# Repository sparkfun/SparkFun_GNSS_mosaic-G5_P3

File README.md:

SparkFun Allband GNSS RTK Breakout - mosaic-G5 P3
========================================

[*SparkFun Allband GNSS RTK Breakout - mosaic-G5 P3 (GPS-29208)*](https://www.sparkfun.com/sparkfun-allband-gnss-rtk-breakout-mosaic-g5-p3.html)

This SparkFun Allband GNSS RTK Breakout features the Septentrio mosaic-G5 P3 GNSS module, a 60% smaller and 40% lower power consumption variant of the mosaic-X5 GNSS module, making it ideal for drone and IoT applications. The receiver supports the GPS (USA), GLONASS (Russia), Beidou (China), Galileo (Europe), and QZSS (Japan) GNSS constellations, including regional systems *(i.e. SBAS)*. With its Real-Time Kinematics (RTK) capabilities, the module can achieve a horizontal accuracy of 6mm (~0.25in), vertical accuracy of 1cm (~0.4in), PPS timing resolution of 1.4ns (1.4 billionths of a second), and event trigger accuracy below 3ns. It also features Septentrio's unique [AIM+ technology](https://www.septentrio.com/en/learn-more/advanced-positioning-technology/aim-jamming-protection) for interference mitigation and anti-spoofing, ensuring best-in-class reliability and scalable position accuracy.

The mosaic-G5 P3 GNSS module supports USB 2.0 communication and two UART interfaces; along with two GPIO, two configurable PPS outputs, and two event trigger input pins. Users can control and configure the GNSS module through a command-line interface (CLI) using the Septentrio Binary Format (SBF), NMEA, and RTCM v3.x protocols. Otherwise, users can also configure the GNSS module with Septentrio's [RxTools software application](https://www.septentrio.com/en/products/gps-gnss-receiver-software/rxtools). On the board, the `UART2` interface is also broken out to a locking JST connector and BlueSMiRF PTH header pins to attach an RF transceiver for RTK corrections.

Documentation
-------------

- **[Hookup Guide (mkdocs)](http://docs.sparkfun.com/SparkFun_GNSS_mosaic-G5_P3/)** - A hookup guide for the SparkFun mosaic-G5 P3 GNSS breakout board hosted by GitHub pages.<br>

Repository Contents
-------------------

- **[/docs](/docs/)** - Online documentation files
  - [/assets](/docs/assets/) - Assets files
    - [/3d_model](/docs/assets/3d_model/) - 3D models for the board
    - [/board_files](/docs/assets/board_files/) - Design files for the board
      - [KiCad Design Files](/docs/assets/board_files/kicad_files.zip) (.zip)
      - [Schematic](/docs/assets/board_files/schematic.pdf) (.pdf)
      - [Dimensions](/docs/assets/board_files/dimensions.pdf) (.pdf)
    - [/component_documentation](/docs/assets/component_documentation/) - Datasheets for hardware components
    - [/img/hookup_guide](/docs/assets/img/hookup_guide/) - Images for hookup guide documentation - Hookup guide images for the board
    - /Hardware - Hardware design files (.brd, .sch)
      - /Production - Production files

Product Variants
----------------

- mosaic-G5 P3:
  - [GPS-29208](https://www.sparkfun.com/sparkfun-allband-gnss-rtk-breakout-mosaic-g5-p3.html) - Allband GNSS RTK Breakout - mosaic-G5 P3
  - Flex Modules:
    - [GPS-29209](https://www.sparkfun.com/sparkpnt-gnss-flex-module-mosaic-g5-p3.html) - GNSS Flex module - mosaic-G5 P3
    - [GPS-29363](https://www.sparkfun.com/sparkpnt-gnss-flex-module-mosaic-g5-p3-im19-imu.html) - GNSS Flex module - mosaic-G5 P3 & IM19
    - [GPS-](https://www.sparkfun.com/sparkfun-gnss-flex-phat-mosaic-g5-p3.html) - GNSS Flex pHAT w/ the mosaic-G5 P3 GNSS Flex module
    - [GPS-](https://www.sparkfun.com/sparkfun-gnss-flex-phat-mosaic-g5-p3-im19-imu.html) - GNSS Flex pHAT w/ the mosaic-G5 P3 & IM19 GNSS Flex module
- mosaic-X5:
  - [GPS-23088](https://www.sparkfun.com/sparkfun-triband-gnss-rtk-breakout-mosaic-x5.html) - Triband GNSS RTK Breakout - mosaic-X5
  - [GPS-23748](https://www.sparkfun.com/sparkfun-rtk-mosaic-x5.html) - RTK mosaic-X5
  - [GPS-24903](https://www.sparkfun.com/sparkpnt-rtk-facet-mosaic-l-band.html) - SparkPNT RTK Facet mosaic L-Band
  - Flex Modules:
    - [GPS-28138](https://www.sparkfun.com/sparkpnt-gnss-flex-module-mosaic-x5.html) - GNSS Flex module - mosaic-X5
    - [GPS-29457](https://www.sparkfun.com/sparkpnt-gnss-flex-module-mosaic-x5-im19-imu.html) - GNSS Flex module - mosaic-X5 & IM19
    - [GPS-28766](https://www.sparkfun.com/sparkfun-gnss-flex-phat-mosaic-x5.html) - GNSS Flex pHAT w/ the mosaic-X5 GNSS Flex module
    - [GPS-29889](https://www.sparkfun.com/sparkfun-gnss-flex-phat-mosaic-x5-im19-imu.html) - GNSS Flex pHAT w/ the mosaic-X5 & IM19 GNSS Flex module
- mosaic-T:
  - [GPS-28731](https://www.sparkfun.com/sparkfun-timing-gnss-breakout-mosaic-t.html) - mosaic-T Timing GNSS Breakout
  - [GPS-26289](https://www.sparkfun.com/sparkpnt-gnss-disciplined-oscillator.html) - GNSS Disciplined Oscillator

|                     | mosaic-G5 P3 | mosaic-X5 | mosaic-T |
| :------------------ | :----------- | :-------- | :------- |
| Breakout Board      | [GPS-29208](https://www.sparkfun.com/sparkfun-allband-gnss-rtk-breakout-mosaic-g5-p3.html) | [GPS-23088](https://www.sparkfun.com/sparkfun-triband-gnss-rtk-breakout-mosaic-x5.html) | [GPS-28731](https://www.sparkfun.com/sparkfun-timing-gnss-breakout-mosaic-t.html) |
| GNSS Flex Module         | [GPS-29209](https://www.sparkfun.com/sparkpnt-gnss-flex-module-mosaic-g5-p3.html)<br>[GPS-30384](https://www.sparkfun.com/sparkfun-gnss-flex-phat-mosaic-g5-p3.html) - pHAT Kit | [GPS-28138](https://www.sparkfun.com/sparkpnt-gnss-flex-module-mosaic-x5.html)<br>[GPS-28766](https://www.sparkfun.com/sparkfun-gnss-flex-phat-mosaic-x5.html) - pHAT Kit | N/A |
| GNSS Flex Module w/ IM19 | [GPS-29363](https://www.sparkfun.com/sparkpnt-gnss-flex-module-mosaic-g5-p3-im19-imu.html)<br>[GPS-30546](https://www.sparkfun.com/sparkfun-gnss-flex-phat-mosaic-g5-p3-im19-imu.html) - pHAT Kit | [GPS-29457](https://www.sparkfun.com/sparkpnt-gnss-flex-module-mosaic-x5-im19-imu.html)<br>[GPS-29889](https://www.sparkfun.com/sparkfun-gnss-flex-phat-mosaic-x5-im19-imu.html) - pHAT Kit | N/A |
| Other               | N/A | [GPS-23748](https://www.sparkfun.com/sparkfun-rtk-mosaic-x5.html) - RTK Platform<br>[GPS-24903](https://www.sparkfun.com/sparkpnt-rtk-facet-mosaic-l-band.html) - Facet | [GPS-26289](https://www.sparkfun.com/sparkpnt-gnss-disciplined-oscillator.html) - GNSSDO |

Version History
---------------

- [v10](https://github.com/sparkfun/SparkFun_GNSS_mosaic-G5_P3/releases/tag/v10) - Initial Release

License Information
-------------------

This product is ***open source***!

Please review the [`LICENSE.md`](./LICENSE.md) file for license information.

If you have any questions or concerns about licensing, please contact technical support on our [SparkFun forums](https://community.sparkfun.com/).

Distributed as-is; no warranty is given.

- Your friends at SparkFun.

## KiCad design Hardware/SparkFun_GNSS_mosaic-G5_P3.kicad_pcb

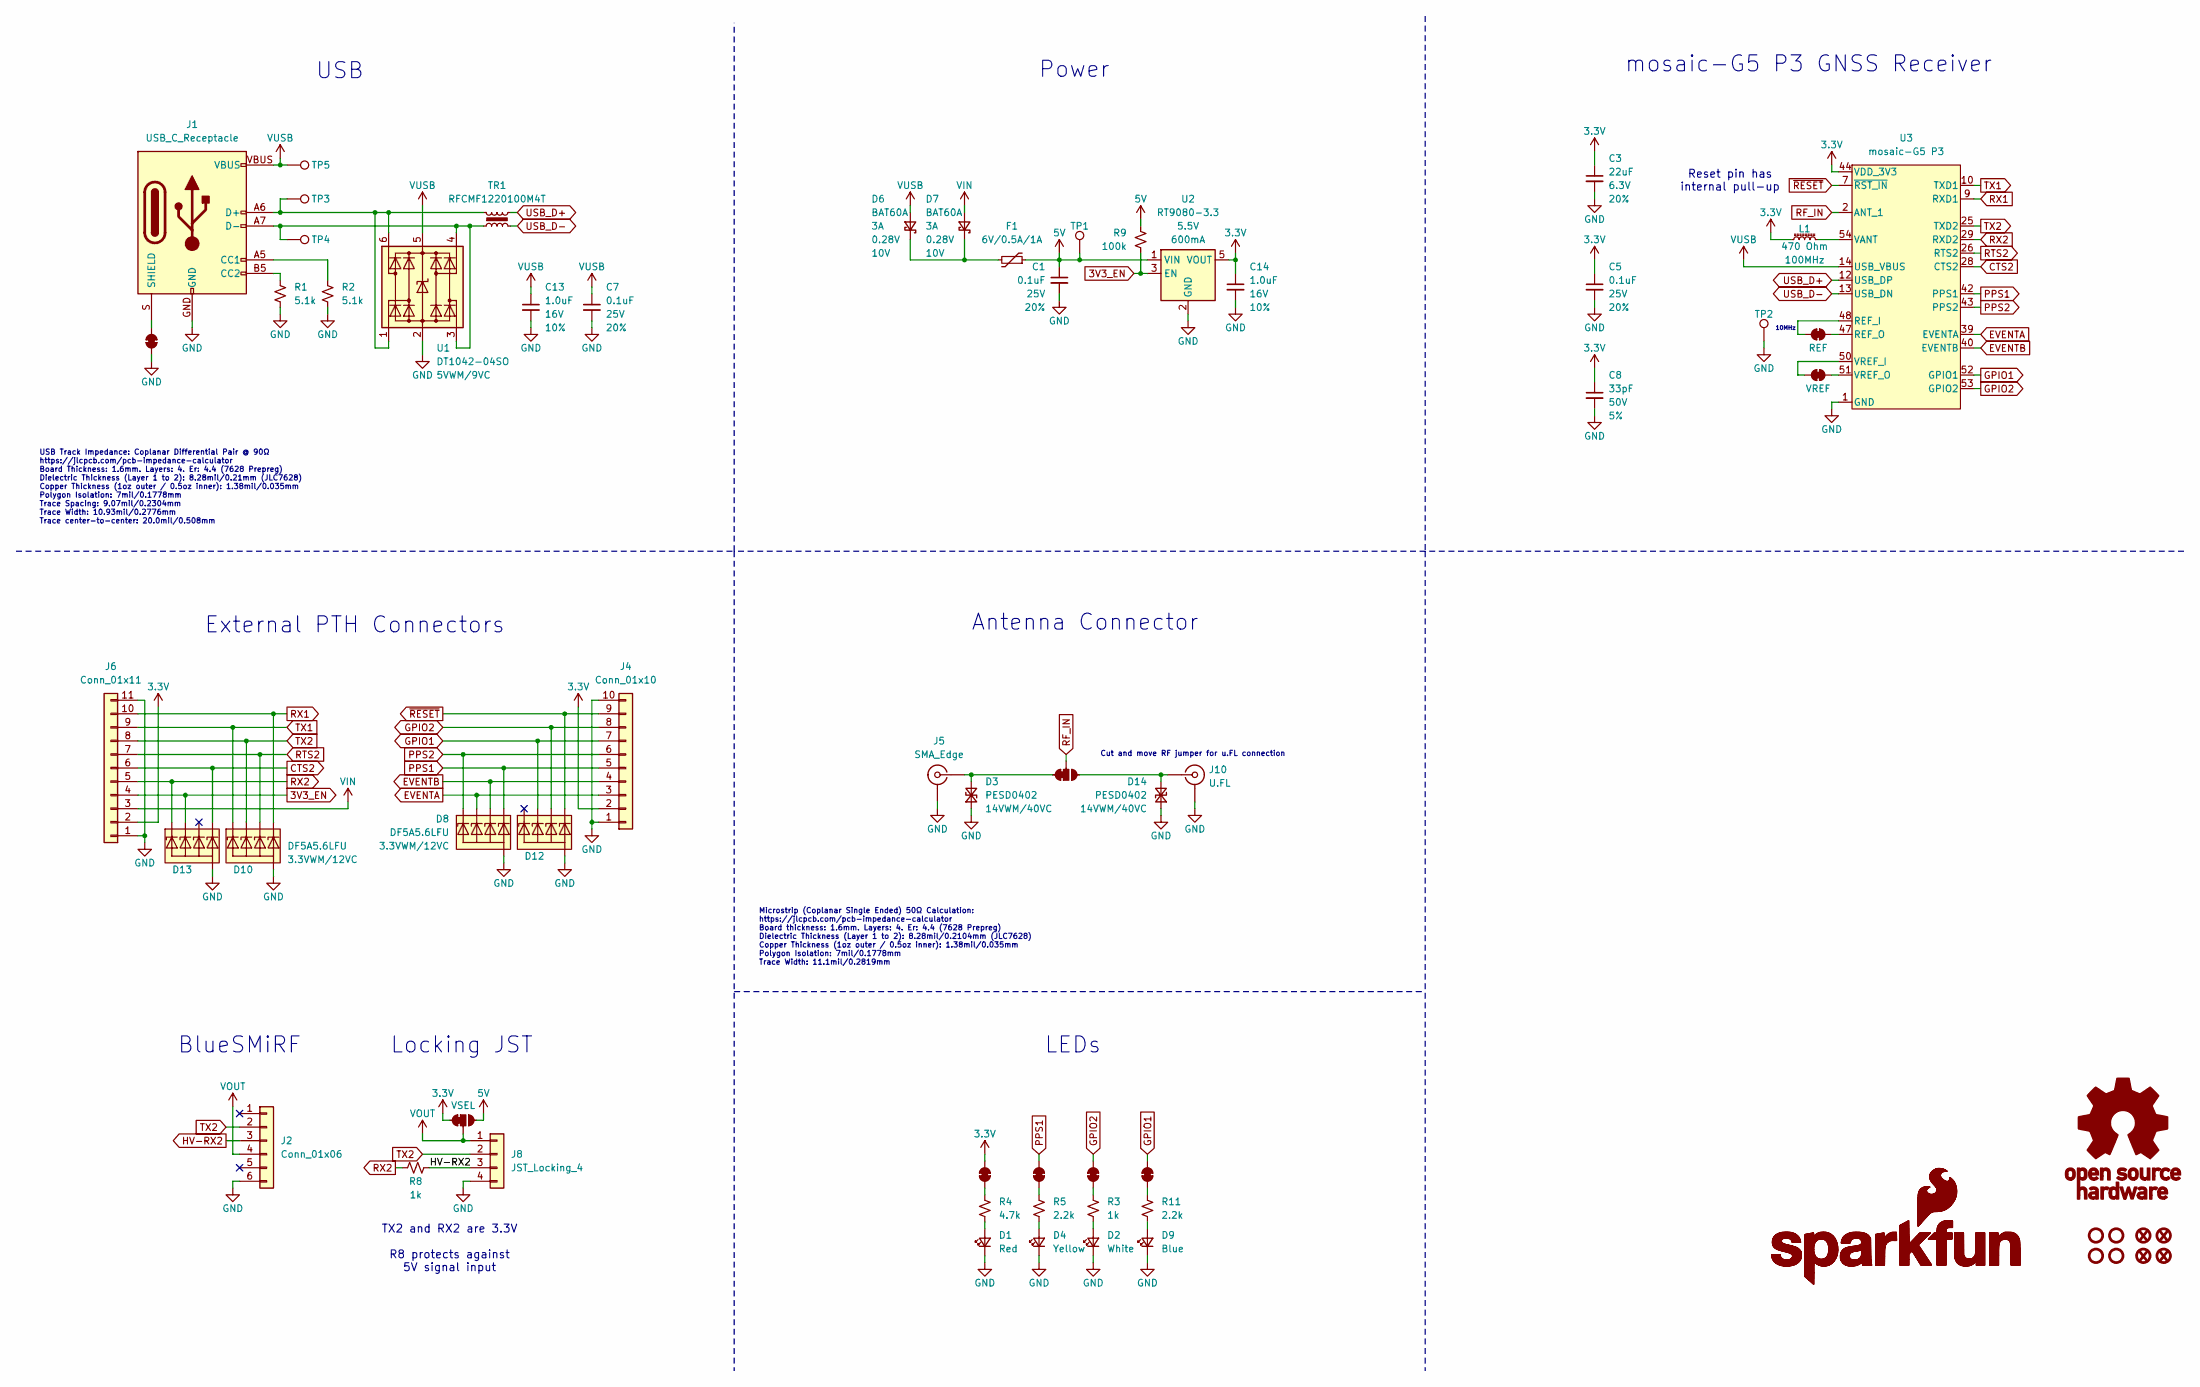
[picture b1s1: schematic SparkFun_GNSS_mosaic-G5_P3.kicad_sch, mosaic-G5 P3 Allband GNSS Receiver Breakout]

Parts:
C1, C5, C7: 0.1uF; C_0603_1608Metric; Voltage 25V; Tolerance 20%
C3: 22uF; C_0603_1608Metric; Voltage 6.3V; Tolerance 20%
C8: 33pF; C_0603_1608Metric; Voltage 50V; Tolerance 5%
C13, C14: 1.0uF; C_0603_1608Metric; Voltage 16V; Tolerance 10%
D1: Red; LED_0603_1608Metric_Red
D2: White; LED_0603_1608Metric_White
D3, D14: PESD0402; C_0402_1005Metric; Rating 14VWM/40VC
D4: Yellow; LED_0603_1608Metric_Yellow
D6, D7: BAT60A; SOD-323
D8, D10, D12, D13: DF5A5.6LFU; SOT-353; Rating 3.3VWM/12VC
D9: Blue; LED_0603_1608Metric_Blue
F1: 6V/0.5A/1A; 0805
FID3, FID4, FID5, FID6: Fiducial_0.5mm; Fiducial_0.5mm_Mask1mm
G1: OSHW_Logo; Creative_Commons_License
G3, G5: SparkFun_Logo
J1: USB_C_Receptacle; USB-C_16
J2: Conn_01x06; 1x06_P2.54mm
J4: Conn_01x10; 1x10_P2.54mm
J5: SMA_Edge; SMA_Edge_6.3mm
J6: Conn_01x11; 1x11_P2.54mm
J8: JST_Locking_4; JST_1x04_P1.25mm_Locking_Horizontal_SMD
J10: U.FL
JP1: Jumper_3_NC-1_Trace
JP2, JP3, JP5, JP7, JP8: Jumper_2_NC_Trace
JP4: VSEL; Jumper_3_NC-1_Trace
L1: 470 Ohm; C_0603_1608Metric
R1, R2: 5.1k; R_0603_1608Metric
R3, R8: 1k; R_0603_1608Metric
R4: 4.7k; R_0603_1608Metric
R5, R11: 2.2k; R_0603_1608Metric
R9: 100k; R_0603_1608Metric
REF.1: REF; Jumper_2_NC_Trace
ST1, ST2, ST3, ST4: Standoff
TP1, TP3, TP4, TP5: 1.0mm; TestPoint-1.0mm
TP2: 1.25mm; TestPoint-1.25mm
TR1: RFCMF1220100M4T; Choke_100MHz_USB
U1: DT1042-04SO; SOT23-6; Rating 5VWM/9VC
U2: RT9080-3.3; SOT23-5
U3: mosaic-G5 P3; Septentrio_mosaic-G5_LGA54
VREF.1: VREF; Jumper_2_NC_Trace

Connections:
3.3V: C3.1, C5.1, C8.1, C14.1, J4.2, J6.2, JP2.2 (B), JP4.1 (A), L1.1, U2.5 (VOUT), U3.44 (VDD_3V3), U3.45 (VDD_3V3)
3V3_EN: D13.3 (K2), J6.4, R9.1, U2.3 (EN)
5V: C1.1, F1.1, JP4.3 (C), R9.2, TP1.1, U2.1 (VIN)
CTS2: D13.5 (K4), J6.6, U3.28 (CTS2)
EVENTA: D8.3 (K2), J4.3, U3.39 (EVENTA)
EVENTB: D8.4 (K3), J4.4, U3.40 (EVENTB)
GND: C1.2, C3.2, C5.2, C7.2, C8.2, C13.2, C14.2, D1.1 (K), D2.1 (K), D3.1 (A1), D4.1 (K), D8.2 (A), D9.1 (K), D10.2 (A), D12.2 (A), D13.2 (A), D14.1 (A1), J1.GND, J2.6, J4.1, J4.10, J5.2 (Ext), J6.1, J6.11, J8.4, J10.2 (Ext), JP7.1 (A), R1.1, R2.1, TP2.1, U1.2 (GND), U2.2 (GND), U3.1 (GND), U3.3 (GND), U3.4 (GND), U3.6 (GND), U3.11 (GND), U3.17 (GND), U3.21 (GND), U3.27 (GND), U3.34 (GND), U3.41 (GND), U3.46 (GND), U3.49 (GND), U3.55 (GND), U3.56 (GND), U3.57 (GND), U3.58 (GND), U3.59 (GND), U3.60 (GND), U3.61 (GND), U3.62 (GND), U3.63 (GND), U3.64 (GND), U3.65 (GND), U3.66 (GND), U3.67 (GND), U3.68 (GND), U3.69 (GND), U3.70 (GND), U3.71 (GND), U3.72 (GND), U3.73 (GND), U3.74 (GND), U3.75 (GND), U3.76 (GND), U3.77 (GND), U3.78 (GND), U3.79 (GND), U3.80 (GND), U3.81 (GND), U3.82 (GND), U3.83 (GND), U3.84 (GND), U3.85 (GND), U3.86 (GND), U3.87 (GND), U3.88 (GND), U3.89 (GND), U3.90 (GND), U3.91 (GND), U3.92 (GND), U3.93 (GND), U3.94 (GND)
GPIO1: D12.3 (K2), J4.7, JP8.2 (B), U3.52 (GPIO1)
GPIO2: D12.4 (K3), J4.8, JP5.2 (B), U3.53 (GPIO2)
HV-RX2: J2.3, J8.3, R8.1
unnamed: D1.2 (A), R4.1
unnamed: D2.2 (A), R3.1
unnamed: D3.2 (A2), J5.1 (In), JP1.1 (A)
unnamed: D4.2 (A), R5.1
unnamed: D6.1 (K), D7.1 (K), F1.2
unnamed: D9.2 (A), R11.1
unnamed: D14.2 (A2), J10.1 (In), JP1.3 (C)
unnamed: J1.A5 (CC1), R2.2
unnamed: J1.B5 (CC2), R1.2
unnamed: J1.S (SHIELD), JP7.2 (B)
unnamed: JP2.1 (A), R4.2
unnamed: JP3.1 (A), R5.2
unnamed: JP5.1 (A), R3.2
unnamed: JP8.1 (A), R11.2
unnamed: REF.1.1 (A), U3.47 (REF_O)
unnamed: REF.1.2 (B), U3.48 (REF_I)
unnamed: J1.A6 (D+), J1.B6 (D+), TP3.1, TR1.3, U1.1 (I/O1), U1.6 (I/O4)
unnamed: J1.A7 (D-), J1.B7 (D-), TP4.1, TR1.1, U1.3 (I/O2), U1.4 (I/O3)
unnamed: L1.2, U3.54 (VANT)
unnamed: U3.50 (VREF_I), VREF.1.2 (B)
unnamed: U3.51 (VREF_O), VREF.1.1 (A)
PPS1: D8.5 (K4), J4.5, JP3.2 (B), U3.42 (PPS1)
PPS2: D8.1 (K1), J4.6, U3.43 (PPS2)
RF_IN: JP1.2 (B), U3.2 (ANT_1)
RTS2: D10.4 (K3), J6.7, U3.26 (RTS2)
RX1: D10.5 (K4), J6.10, U3.9 (RXD1)
RX2: D13.1 (K1), J6.5, R8.2, U3.29 (RXD2)
TX1: D10.1 (K1), J6.9, U3.10 (TXD1)
TX2: D10.3 (K2), J2.2, J6.8, J8.2, U3.25 (TXD2)
USB_D+: TR1.4, U3.12 (USB_DP)
USB_D-: TR1.2, U3.13 (USB_DN)
VIN: D7.2 (A), J6.3
VOUT: J2.4, J8.1, JP4.2 (B)
VUSB: C7.1, C13.1, D6.2 (A), J1.VBUS, TP5.1, U1.5 (VCC), U3.14 (USB_VBUS)
~RESET: D12.5 (K4), J4.9, U3.7 (~RST_IN)

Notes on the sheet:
TX2 and RX2 are 3.3V R8 protects against 5V signal input
Microstrip (Coplanar Single Ended) 50Ω Calculation: https://jlcpcb.com/pcb-impedance-calculator Board thickness: 1.6mm. Layers: 4. Er: 4.4 (7628 Prepreg) Dielectric Thickness (Layer 1 to 2): 8.28mil/0.2104mm (JLC7628) Copper Thickness (1oz outer / 0.5oz inner): 1.38mil/0.035mm Polygon Isolation: 7m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
USB Track Impedance: Coplanar Differential Pair @ 90Ω https://jlcpcb.com/pcb-impedance-calculator Board Thickness: 1.6mm. Layers: 4. Er: 4.4 (7628 Prepreg) Dielectric Thickness (Layer 1 to 2): 8.28mil/0.21mm (JLC7628) Copper Thickness (1oz outer / 0.5oz inner): 1.38mil/0.035mm Polygon Isolation: 7m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
Cut and move RF jumper for u.FL connection
BlueSMiRF
Reset pin has internal pull-up
Locking JST
10MHz
Power
Antenna Connector
LEDs
mosaic-G5 P3 GNSS Receiver
USB
External PTH Connectors

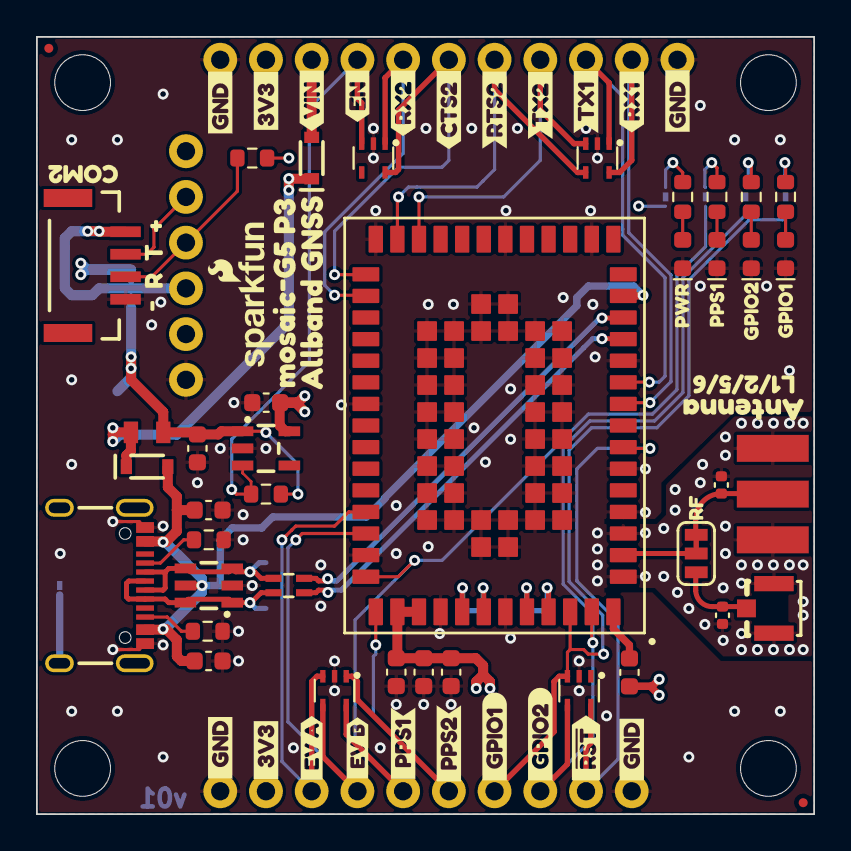
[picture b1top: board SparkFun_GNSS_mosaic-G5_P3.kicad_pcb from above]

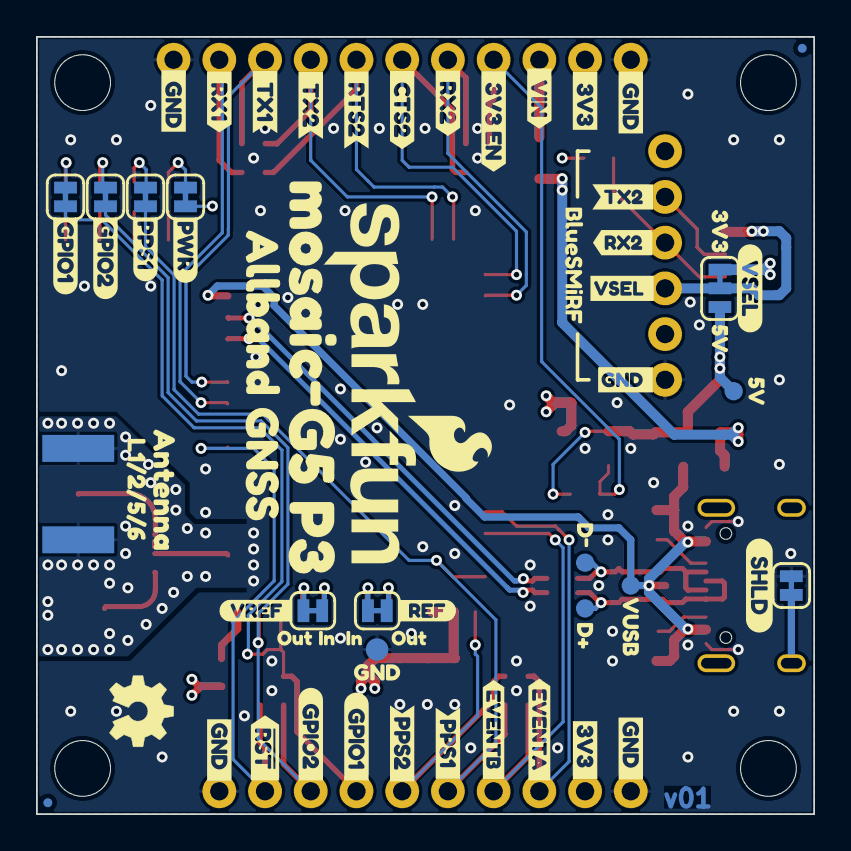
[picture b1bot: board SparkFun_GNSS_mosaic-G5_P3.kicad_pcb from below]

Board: 4 copper layers, 43.2 x 43.2 mm, 145 parts (65 on the bottom side), 45 nets.

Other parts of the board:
Ref**: Val**; OSHW_Logo_4mm
kibuzzard-64C3DF93: G***; kibuzzard-64C3DF93
kibuzzard-66CB82FB: G***; kibuzzard-66CB82FB
kibuzzard-66CB829C: G***; kibuzzard-66CB829C
kibuzzard-66CB830B, kibuzzard-66CB830B#2: G***; kibuzzard-66CB830B
kibuzzard-67EC56CE, kibuzzard-67EC56CE#2: G***; kibuzzard-67EC56CE
kibuzzard-67EC56E0, kibuzzard-67EC56E0#2: G***; kibuzzard-67EC56E0
kibuzzard-67EC5586: G***; kibuzzard-67EC5586
kibuzzard-67EC5701: G***; kibuzzard-67EC5701
kibuzzard-67ED9C3D: G***; kibuzzard-67ED9C3D
kibuzzard-67ED9D32: G***; kibuzzard-67ED9D32
kibuzzard-67ED93D1: G***; kibuzzard-67ED93D1
kibuzzard-680A6E0E: G***; kibuzzard-680A6E0E
kibuzzard-680A6E23: G***; kibuzzard-680A6E23
kibuzzard-680A70A3: G***; kibuzzard-680A70A3
kibuzzard-680A70AF: G***; kibuzzard-680A70AF
kibuzzard-680A70C6: G***; kibuzzard-680A70C6
kibuzzard-680A7093: G***; kibuzzard-680A7093
kibuzzard-6501FDDA: G***; kibuzzard-6501FDDA
kibuzzard-6797D0AD, kibuzzard-6797D0AD#2: G***; kibuzzard-6797D0AD
kibuzzard-6797D04A: G***; kibuzzard-6797D04A
kibuzzard-6797D04F: G***; kibuzzard-6797D04F
kibuzzard-6797D058: G***; kibuzzard-6797D058
kibuzzard-6797D071: G***; kibuzzard-6797D071
kibuzzard-68093EBD: G***; kibuzzard-68093EBD
kibuzzard-68093ED7: G***; kibuzzard-68093ED7
kibuzzard-68093EFA: G***; kibuzzard-68093EFA
kibuzzard-68093F05: G***; kibuzzard-68093F05
kibuzzard-68093F52: G***; kibuzzard-68093F52
kibuzzard-68093F83: G***; kibuzzard-68093F83
kibuzzard-68094D97: G***; kibuzzard-68094D97
kibuzzard-68094DBD: G***; kibuzzard-68094DBD
kibuzzard-68094F29: G***; kibuzzard-68094F29
kibuzzard-68094F93: G***; kibuzzard-68094F93
kibuzzard-68094FA9: G***; kibuzzard-68094FA9
kibuzzard-680915DD: G***; kibuzzard-680915DD
kibuzzard-680918A4: G***; kibuzzard-680918A4
kibuzzard-680918BB: G***; kibuzzard-680918BB
kibuzzard-680918D3: G***; kibuzzard-680918D3
kibuzzard-680918E6: G***; kibuzzard-680918E6
kibuzzard-680918FA: G***; kibuzzard-680918FA
kibuzzard-680933A4: G***; kibuzzard-680933A4
kibuzzard-680933E9: G***; kibuzzard-680933E9
kibuzzard-680934E6: G***; kibuzzard-680934E6
kibuzzard-680942C8: G***; kibuzzard-680942C8
kibuzzard-680942CE: G***; kibuzzard-680942CE
kibuzzard-680943A7: G***; kibuzzard-680943A7
kibuzzard-680943B2: G***; kibuzzard-680943B2
kibuzzard-680943F0: G***; kibuzzard-680943F0
kibuzzard-680943F9: G***; kibuzzard-680943F9
kibuzzard-680973E5: G***; kibuzzard-680973E5
kibuzzard-680973FC: G***; kibuzzard-680973FC
kibuzzard-680974A3: G***; kibuzzard-680974A3
kibuzzard-6809340B: G***; kibuzzard-6809340B
kibuzzard-6809427A, kibuzzard-6809427A#2: G***; kibuzzard-6809427A
kibuzzard-6809432A: G***; kibuzzard-6809432A
kibuzzard-6809434D: G***; kibuzzard-6809434D
kibuzzard-6809441F: G***; kibuzzard-6809441F
kibuzzard-6809448B: G***; kibuzzard-6809448B
kibuzzard-68092547: G***; kibuzzard-68092547
kibuzzard-68093375, kibuzzard-68093375#2: G***; kibuzzard-68093375
kibuzzard-68093382, kibuzzard-68093382#2: G***; kibuzzard-68093382
kibuzzard-68093452: G***; kibuzzard-68093452
kibuzzard-68093461: G***; kibuzzard-68093461
kibuzzard-68093499: G***; kibuzzard-68093499
kibuzzard-68093505: G***; kibuzzard-68093505
kibuzzard-68093510: G***; kibuzzard-68093510
kibuzzard-68094376: G***; kibuzzard-68094376
kibuzzard-68094382: G***; kibuzzard-68094382
kibuzzard-68094414: G***; kibuzzard-68094414
kibuzzard-68094456: G***; kibuzzard-68094456
kibuzzard-68094468: G***; kibuzzard-68094468
kibuzzard-68094496: G***; kibuzzard-68094496
kibuzzard-68095184: G***; kibuzzard-68095184
kibuzzard-68097087: G***; kibuzzard-68097087

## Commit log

2025-04-23 Panelized
2025-04-24 Ready for protos
2025-04-24 Re-panelized with paste reduction
2025-09-10 Update symbols and 3D models
2025-09-10 Fix RFCMF1220100M4T pin numbering
2025-09-10 Use updated (plotted) schematic
2025-10-23 Update to latest SparkFun KiCad Libraries
2026-02-19 Docs - Initial Commit
    Initial commit of the files to generate the hookup guide
2026-02-19 Deployed b2c47d3 with MkDocs version: 1.6.1
2026-02-19 Docs fix
    Fix docs build
2026-02-19 Deployed 261b499 with MkDocs version: 1.6.1
2026-06-03 Deployed 4d60c7a with MkDocs version: 1.6.1

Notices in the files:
parts and their libraries:
https://creativecommons.org/licenses/by-sa/4.0
Released under the Creative Commons Attribution Share-Alike 4.0 License
